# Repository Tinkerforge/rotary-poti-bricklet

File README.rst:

Rotary Poti Bricklet
====================

This repository contains the firmware source code and the hardware design
files. The documentation generator configs can be found at
https://github.com/Tinkerforge/generators

Repository Content
------------------

software/:
 * examples/: Examples for all supported languages
 * build/: Compiled files
 * src/: Source code of firmware
 * Makefile: Makefile to build project

hardware/:
 * Contains KiCad project files and additionally schematics as PDF

datasheets/:
 * Contains datasheets for sensors and complex ICs that are used

Hardware
--------

The hardware is designed with the open source EDA Suite KiCad
(http://www.kicad.org). Before you are able to open the files,
you have to install the Tinkerforge kicad-libraries
(https://github.com/Tinkerforge/kicad-libraries). You can either clone
them directly in hardware/ or clone them in a separate folder and
symlink them into hardware/
(ln -s kicad_path/kicad-libraries project_path/hardware). After that you
can open the .pro file in hardware/ with KiCad and from there view and
modify the schematics and the PCB layout.

Software
--------

If you want to do your own Brick/Bricklet firmware development we highly
recommend that you use our build environment setup script and read the
tutorial (https://www.tinkerforge.com/en/doc/Tutorials/Tutorial_Build_Environment/Tutorial.html).

To compile the C code we recommend you to install the newest GNU Arm Embedded
Toolchain (https://launchpad.net/gcc-arm-embedded/+download).
You also need to install bricklib (https://github.com/Tinkerforge/bricklib)
and brickletlib (https://github.com/Tinkerforge/brickletlib).

You can either clone it directly in software/src/ or clone it in a
separate folder and symlink it into software/src/
(ln -s bricklib_path/bricklib project_path/software/src/ and
ln -s brickletlib_path/brickletlib project_path/software/src/).
Finally make sure to have CMake installed
(http://www.cmake.org/cmake/resources/software.html).

After that you can build the firmware by invoking make in software/.
The firmware (.bin) can then be found in software/build/ and uploaded
with brickv (click button "Flashing" on start screen).

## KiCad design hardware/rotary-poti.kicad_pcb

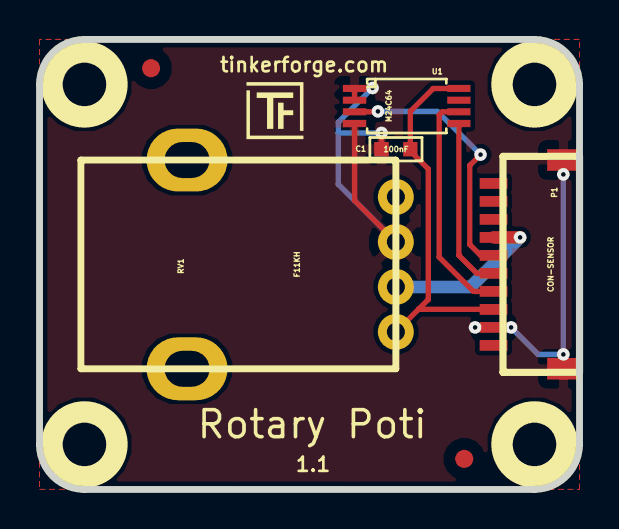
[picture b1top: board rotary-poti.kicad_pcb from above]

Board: 2 copper layers, 30.0 x 25.0 mm, 13 parts (0 on the bottom side), 6 nets.

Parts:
C1: 100nF; 0603
Fiducial_Mark: VAL**; Fiducial_Mark
Fiducial_Mark#2: VAL**; Fiducial_Mark
P1: CON-SENSOR
RV1: F11KH
Ref**: Val**; Logo_31x31
U1: M24C64; TSSOP8
U2, U3, U4, U5: DRILL; DRILL_NP
VAL: CE_5mm
VAL#2: WEEE_7mm

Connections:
GND: C1.1, P1.2, P1.EP, RV1.3, U1.1, U1.2, U1.4
IN_1: P1.7, RV1.2
unnamed: P1.6, U1.3
SCL: P1.4, U1.6
SDA: P1.5, U1.5
VCC: C1.2, P1.3, RV1.1, U1.8

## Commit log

2011-08-25 initial hardware source commit
2011-08-25 add project description
2011-09-01 wrong datasheet deleted
2011-09-05 Remove offset because of better optimization in newer gccs
2011-09-12 fix c&p error in description (illuminiscence -> position)
2011-09-13 add java bindings and examples
2011-09-14 limit line length of java examples to 100 characters
2011-09-23 Add C# examples and bindings
2011-10-05 Remove Bindings and IP Connection (these are generated and they change too often) and rename bindings to examples
2011-10-05 add tinkerforge package to python imports
2011-10-06 remove faulty gcc commandline invocation
2011-10-06 add firmware version and name
2012-02-13 check in of version V1.1 - remove address line resistor - add fiducials on board
2012-02-14 add compatability for different tick types
2012-02-15 Add changelog
2012-02-15 Move software changelog to software folder
2012-04-25 Unify capitalization of "IP connection" in examples
2012-05-09 Add PHP examples
2012-05-14 java: Remove unnecessary new String(...) calls
2012-05-25 Add Ruby examples
2012-06-05 Fix register_callback syntax error in Ruby examples on Windows
2012-06-12 Use correct term 'Bricklet' in example code error message
2012-06-12 Prefer IPConnection destroy over join_thread
2012-07-01 Add generate_makefile.bat for windows
2012-07-25 Add Delphi examples
2012-08-08 delphi: Add comment about UID
2012-10-24 Make cmake find the correct objcopy binary
    On some systems cmake uses the wrong objcopy binary, tell it to use
    the correct one.
2012-11-13 Support for protocol 2.0
2012-11-29 Make examples compatible to Protocol V2.0
2012-11-29 Make Ruby examples Protocol 2.0 compatible
2012-11-29 Make C examples Protocol 2.0 compatible
2012-11-29 Make Java examples Protocol 2.0 compatible
2012-11-29 Make PHP examples Protocol 2.0 compatible
2012-11-29 Make Delphi/Pascal examples Protocol 2.0 compatible
2012-11-30 delphi: Remove unnecessary parentheses and call destructor again
2012-12-05 Add protocol 2.0 compatability to C# bindings
2012-12-06 Fix C example
2012-12-11 Avoid g++ warnings about missing casts in C examples
2012-12-21 Add .gitignore
2013-01-09 Use specific device object for callbacks
2013-01-17 Make Java examples compatible to new listener approach
2013-01-28 Update outdated comment in Java example
2013-02-07 Use IPconnection disconnect explicitly in examples
2013-02-13 Fix typo in examples
2013-02-18 Add Visual Basic .NET examples
2013-05-15 Don't send threshold callback twice
    Fixed in brickletlib.
2013-08-13 Add shell examples
2013-08-21 windows: Don't trigger a build in generate_makefile.bat
    Also use normal make instead of a special named one.
2013-12-19 Fix wrong length for GetDebounce packet (through brickletlib)
2014-01-06 Add static assert for BrickContext size
2014-01-10 Add Perl examples
2014-01-15 php: Use const for constant values
2014-02-07 Add Mathematica examples
2014-02-10 perl: fixed namespace
2014-02-12 javascript: add examples
2014-02-18 javascript: examples fixed
2014-02-20 javascript: add html exmaples
2014-02-24 javascript: port 4280, startExample()
2014-02-28 javascript: Break long lines and cleanup whitespace
2014-03-05 Add LabVIEW examples
2014-03-06 labview: Fix example
2014-03-06 labview: Add examples in LV2010 format
2014-03-25 matlab: add examples
2014-04-02 java: Unify constants style
2014-04-02 perl: Unify print style
2014-04-17 matlab: Adapt examples to new callback style
2014-04-17 matlab: Add parentheses to make pygments happy
2014-04-17 matlab: Fix string in Octave
2014-07-15 java: Replace System.console() usage with an Eclipse compatible pattern
2014-12-02 Use ReadLine instead of ReadKey for C# example
2015-02-13 vbnet: Use ReadLine instead of ReadKey
    Because ReadKey doesn't work with a pipe as stdin on the RED Brick.
2015-03-02 windows: Stop cmake from searching for mingw32-make.exe
    Using MinGW Makefiles as generator makes cmake search for mingw32-make.exe
    which might not be installed because GnuWin32's make.exe is used instead.
2015-03-26 checkin of latest production files
2015-04-09 c: Whitespace
2015-06-24 javascript: Clean up output creation
2015-06-29 octave: Handle short difference between Octave 3.6 and 3.8
    In Octave 3.6 a short is not automatically handled as a number.
2015-07-25 Make JavaScript browser example textarea readonly
2015-07-27 Cleanup C/C++, C#, Java, Python and Ruby examples
2015-07-29 Reformat changelog
2015-07-30 Unify range comment in C/C++, C#, Java, Python and Ruby examples
2015-08-07 Use full device class name in Python examples
2015-08-12 Fix minor warnings in C/C++ examples
2015-08-14 Cleanup Delphi examples
2015-08-18 Cleanup VB.NET examples
2015-08-19 Cleanup Perl examples
2015-08-21 Use shorter print statement in Perl example
2015-09-09 Duplicate cmake call to fix bug during cmake creation
2015-09-30 Generator based example cleanup
2015-11-12 matlab: Fix callback handling for R2014a
    http://undocumentedmatlab.com/blog/matlab-callbacks-for-java-events-in-r2014a
2015-11-25 Include date and commit into changelog
2016-05-18 c: Add missing device destroy call
2016-07-01 Make the change UID comment more explicit
2017-04-13 csharp: Adapt example
2017-05-22 change to new file format
2017-06-02 octave: Use javaObject instead of deprecated java_new
2017-11-30 Update examples from generator
2017-12-07 mathematica: Also generate .nb files
2018-02-02 Update examples
2018-02-19 javascript: Close div tag correctly
2018-02-20 Cleanup KiCad libraries config
    Ensure LibDir=kicad-libraries and LibName1=tinkerforge.
    Remove special library.
2018-05-24 perl: Use strict in examples
2018-07-11 Add Makefile with docker support
2018-07-11 Remove obsolete generate_makefile scripts
2018-07-11 Update directory structure and build instructions
2018-11-06 Add rust examples
2018-11-07 rust: Accept host names for ip connection, fix naming inconsistencies
2018-11-07 rust: Rename callback receivers.
2018-12-14 Add go examples.
2018-12-18 go: Change import path.
2018-12-18 go: Change import path again.
2018-12-20 rust: Reformat examples.
2019-01-24 mqtt: Add examples.
2019-01-24 mqtt: Fix example header.
2019-01-24 mqtt: Remove executable bit in example permissions.
2019-01-24 go: Minor example fixes.
2019-01-24 mqtt: Minor example fixes.
2019-03-28 mqtt: Fix whitespace.
2019-06-04 Correctly handle the fist tick in position_from_analog_value.
    The old behaviour tried to calculate the average over the last analog
    values even if there where no old values accumulated yet. This resulted
    in two sent callbacks if the user could register and activate a
    callback fast enough.
2019-06-04 Update changelog.
2019-06-04 Add commit ref to changelog.
2019-08-22 c: Adapt to bindings changes
2020-01-13 examples: Use python3 input instead of python2 raw_input.
2020-01-13 examples: mqtt: Remove trailing whitespace.
2021-10-25 Update KiCad link
    https://www.kicad.org/blog/2021/10/Avoid-links-to-former-kicad-domain/
2022-05-10 go: Fix format string
2022-07-06 Add license files.

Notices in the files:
hardware/rotary-poti.kicad_pcb:
Licensed under CERN OHL v.1.1
Copyright (©) 2011, B.Nordmeyer
Copyright Tinkerforge GmbH 2011.
This documentation describes Open Hardware and is licensed under the
CERN OHL v. 1.1.
